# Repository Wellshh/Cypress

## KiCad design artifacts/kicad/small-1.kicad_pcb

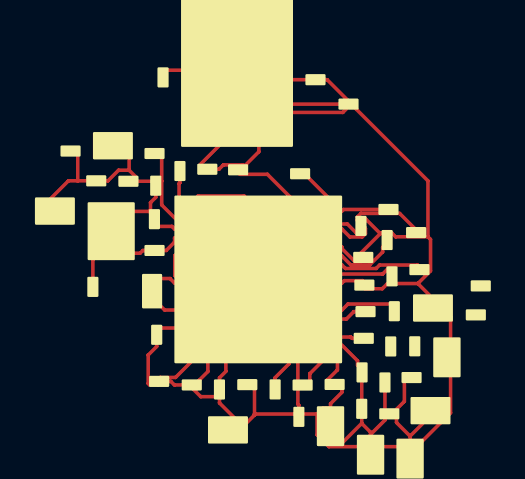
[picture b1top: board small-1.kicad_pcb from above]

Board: 2 copper layers, 57 parts (0 on the bottom side), 35 nets.

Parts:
C2779: C2779
C2781: C2781
C2782: C2782
C2783: C2783
C3780: C3780
C3782: C3782
C3783: C3783
C3784: C3784
C3785: C3785
C3786: C3786
C3787: C3787
C3788: C3788
C3789: C3789
C3790: C3790
C3791: C3791
C3792: C3792
C3795: C3795
C3796: C3796
C3797: C3797
C3798: C3798
C3799: C3799
C3800: C3800
C3801: C3801
C3802: C3802
C3803: C3803
C3804: C3804
C3824: C3824
LB55: LB55
R3729: R3729
R4389: R4389
R4390: R4390
R4392: R4392
R4553: R4553
R4556: R4556
R4557: R4557
R4566: R4566
R4568: R4568
R4570: R4570
R4571: R4571
R4573: R4573
R4574: R4574
R4575: R4575
R4576: R4576
R4577: R4577
R4578: R4578
R4579: R4579
R5027: R5027
R5029: R5029
R5677: R5677
R5820: R5820
R5821: R5821
R5823: R5823
R5908: R5908
R5909: R5909
U382: U382
U383: U383
Y7: Y7

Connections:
GP_I210_SPI_RST_L: R3729.1, U382.1
JTAG_I210_TDO: R5908.1, U383.25
L_I210_GBE0_LINK100_L: R5821.1, U383.28
L_I210_GBE0_LINK_ACT_L: R5823.1, U383.29
NET_1V5_I210: C3795.0, C3797.0, C3799.0, C3801.0, C3803.0, C3824.0, U383.5, U383.6, U383.7
NET_3V3_I210: C3782.0, C3785.0, C3786.0, C3787.0, C3788.0, C3789.0, C3790.0, C3791.0, LB55.0, U383.8, U383.9, U383.10, U383.11, U383.12
NET_3V3_I210_PMOS: C2782.0, C3780.0, LB55.1, R3729.0, R4566.0, R4568.0, R4571.0, R4573.0, R4575.0, R4577.0, R4579.0, R5027.0, R5029.0, R5821.0, R5823.0, R5908.0, R5909.0, U382.0
PCIE_I210_SOC_0AN_C: C3784.1, U383.32
PCIE_I210_SOC_0AP_C: C3783.1, U383.33
SE_I210_CBOT: C2783.0, U383.36
SE_I210_CTOP: C2783.1, U383.37
SE_I210_PCIE_DIS_L: R4566.1, U383.38
SE_I210_XTAL_IN: R5677.0, U383.39
SE_I210_XTAL_IN_R: C2779.0, R5677.1, Y7.0
SE_I210_XTAL_OUT: R4389.0, U383.40
SE_I210_XTAL_OUT_R: C2781.0, R4389.1, Y7.1
SE_NCSI_I210_CLK_IN: R4574.0, U383.41
SE_NCSI_I210_CRS_DV: R4576.0, U383.42
SE_NCSI_I210_RXD0: R4579.1, U383.43
SE_NCSI_I210_RXD1: R4577.1, U383.44
SE_NCSI_I210_TXD0: R4575.1, U383.45
SE_NCSI_I210_TXD1: R4573.1, U383.46
SE_NCSI_I210_TX_EN: R4578.0, U383.47
SE_SPI_I210_MISO_FLASH_R: R4553.1, U382.5
SE_SPI_I210_MUX_CLK_R: R4390.1, U383.48
SE_SPI_I210_MUX_CS_L_R: R4392.1, U383.49
SE_SPI_I210_MUX_MOSI_R: R4556.1, U383.51
SE_SPI_PROG_I210_HOLD_L_PU: R5029.1, U382.6
SE_SPI_PROG_I210_WP_L: R5027.1, U382.7
S_I210_CPLD_WAKE_L: R4568.1, U383.58
S_I210_DEV_OFF_L: R4571.1, U383.59
S_I210_PE_RST_L: R4570.0, U383.60
S_I210_RESET_L: R5820.0, U383.61
S_I210_RSET: R4557.0, U383.62
S_I210_SMB_ALERT_L: R5909.1, U383.63

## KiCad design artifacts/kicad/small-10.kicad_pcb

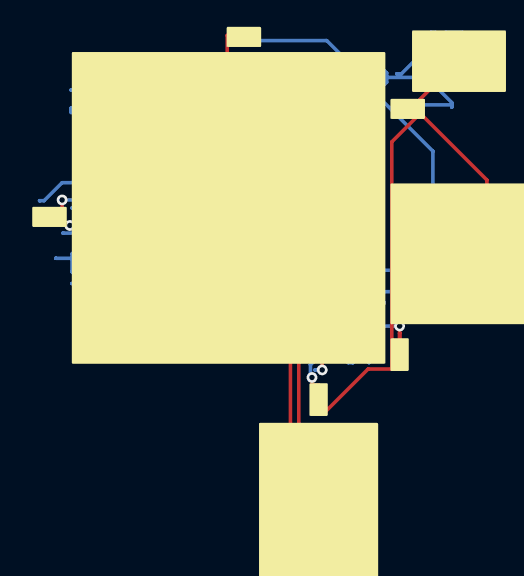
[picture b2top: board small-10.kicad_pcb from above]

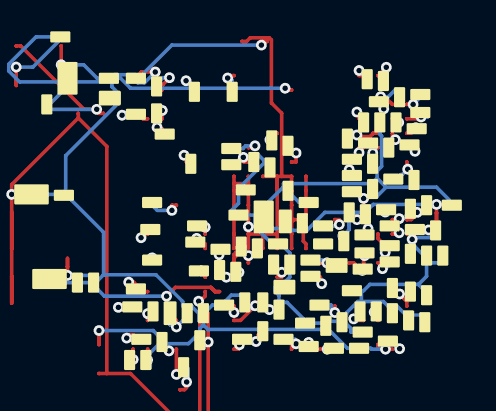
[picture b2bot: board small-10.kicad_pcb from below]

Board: 2 copper layers, 136 parts (127 on the bottom side), 93 nets.

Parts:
C226: C226
C232: C232
C233: C233
C234: C234
C235: C235
C236: C236
C237: C237
C238: C238
C239: C239
C240: C240
C241: C241
C242: C242
C243: C243
C244: C244
C245: C245
C246: C246
C247: C247
C248: C248
C249: C249
C250: C250
C251: C251
C252: C252
C253: C253
C254: C254
C255: C255
C3706: C3706
C3707: C3707
C3708: C3708
C4411: C4411
C4412: C4412
C4413: C4413
C4414: C4414
C4415: C4415
C4416: C4416
C4417: C4417
C4418: C4418
C4419: C4419
C4420: C4420
C4421: C4421
C4422: C4422
C4423: C4423
DS171: DS171
DS172: DS172
J10: J10
J169: J169
LB8: LB8
LB9: LB9
LB31: LB31
R1180: R1180
R1181: R1181
R1191: R1191
R1192: R1192
R1193: R1193
R1194: R1194
R1195: R1195
R1196: R1196
R1197: R1197
R1198: R1198
R1199: R1199
R1200: R1200
R1201: R1201
R1202: R1202
R1203: R1203
R1204: R1204
R1206: R1206
R1207: R1207
R1208: R1208
R1212: R1212
R1213: R1213
R1217: R1217
R1218: R1218
R1219: R1219
R1220: R1220
R1221: R1221
R1222: R1222
R1223: R1223
R1225: R1225
R1226: R1226
R1234: R1234
R1236: R1236
R1238: R1238
R1241: R1241
R1243: R1243
R1244: R1244
R1246: R1246
R1248: R1248
R1249: R1249
R1250: R1250
R1253: R1253
R1301: R1301
R1302: R1302
R2379: R2379
R2380: R2380
R2453: R2453
R2482: R2482
R2823: R2823
R2824: R2824
R2827: R2827
R3286: R3286
R3340: R3340
R3341: R3341
R3342: R3342
R3829: R3829
R3830: R3830
R4106: R4106
R4226: R4226
R4327: R4327
R4329: R4329
R4413: R4413
R4414: R4414
R4497: R4497
R4500: R4500
R4501: R4501
R4649: R4649
R4652: R4652
R4653: R4653
R4654: R4654
R4655: R4655
R4685: R4685
R4695: R4695
R4697: R4697
R4730: R4730
R4732: R4732
R4733: R4733
R4734: R4734
R4735: R4735
R4736: R4736
R4737: R4737
R4738: R4738
R4739: R4739
R4740: R4740
R4766: R4766
R4767: R4767
R4768: R4768
U55: U55
Y4: Y4

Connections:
AG_CPLD_FAN_PWM1_R: R1217.1, U55.31
AG_CPLD_FAN_PWM2_R: R1218.1, U55.32
AG_CPLD_FAN_PWM3_R: R1219.1, U55.33
AG_CPLD_FAN_PWM4_R: R1220.1, U55.34
GP_CEX_REFCLK1_EN: R3829.0, U55.50
GP_CLK_BRD1_RSRVD1_R: R2824.1, U55.55
GP_CLK_BRD1_RSRVD2_R: R4695.1, U55.56
GP_CLK_BRD2_RSRVD1_R: R4106.1, U55.60
GP_CLK_BRD2_RSRVD2_R: R4697.1, U55.61
GP_CPLD_CEX_GPI1_R: R1208.1, U55.66
GP_CPLD_CEX_GPI3_R: R1206.1, U55.68
GP_MAIN_CPLD_HW_REV1: R1234.0, U55.140
GP_MAIN_CPLD_HW_REV2: R1236.0, U55.141
GP_MAIN_CPLD_HW_REV3: R1238.0, U55.142
GP_MAIN_PORTS1_CPLD_FW_RST_L: R1212.0, U55.143
GP_MAIN_PORTS1_CPLD_RST_L: R2379.0, U55.144
GP_MAIN_PORTS2_CPLD_FW_RST_L: R1213.0, U55.145
GP_MAIN_PORTS2_CPLD_RST_L: R2380.0, U55.146
GP_MAIN_PORTS3_CPLD_FW_RST_L: R4652.0, U55.147
GP_MAIN_PORTS3_CPLD_RST_L: R4653.0, U55.148
GP_PPS_IN_LVL_EN_L_R: R4730.1, U55.150
GP_PPS_OUT_LVL_EN_L_R: R4732.1, U55.151
GP_SECURED_DIS_JUMPER: R4327.0, U55.160
GP_SECURED_DIS_JUMPER_IN: J169.2, R4327.1, R4329.0
GP_SPI_JUMPER1: J10.0, R1192.1, U55.163
GP_SPI_JUMPER2: J10.1, R1191.1, U55.164
GP_STRAP_FLASH_PRESENT_R: R1249.1, U55.165
I2C_ASIC_CPLD_M_MDC5_R: R1226.1, U55.176
I2C_ASIC_CPLD_M_MDIO5_R: R1225.1, U55.177
L_CPLD_JTAG_ENB: R1195.1, U55.192
L_CPLD_MAIN_SN_PU: R1253.1, U55.193
L_CPLD_M_DONE: R1194.1, U55.194
L_CPLD_M_INITN_L: C226.0, R1193.1, U55.195
L_CPLD_M_PROGRAMN_L: R1196.1, U55.196
L_MAIN_CPLD_LED0_L: R1180.0, U55.210
L_MAIN_CPLD_LED0_L_R: DS171.1, R1180.1
L_MAIN_CPLD_LIVE_LED_L: R1181.0, U55.211
L_MAIN_CPLD_LIVE_LED_L_R: DS172.1, R1181.1
NET_1V8_VDDIO: C244.0, C246.0, C248.0, LB9.1
NET_3.3V_CPLD_MAIN: C235.0, C236.0, C237.0, C238.0, C239.0, C240.0, C241.0, C242.0, C243.0, C245.0, C247.0, C249.0, C250.0, C252.0, C254.0, C4411.0, C4412.0, C4413.0, C4414.0, C4415.0, C4416.0, C4417.0, C4418.0, C4419.0, C4420.0, C4421.0, C4422.0, C4423.0, LB8.0, U55.2, U55.3, U55.4, U55.5, U55.6, U55.7, U55.8, U55.9, U55.10, U55.11, U55.12, U55.13, U55.14, U55.15, U55.16, U55.17, U55.18, U55.19, U55.20, U55.21, U55.22, U55.23, U55.24, U55.25, U55.26, U55.27, U55.28, U55.29, U55.30
NET_3V3_AUX: C232.0, C233.0, C234.0, C3706.0, DS171.0, DS172.0, J169.0, J169.1, LB8.1, LB31.0, R1191.0, R1192.0, R1193.0, R1194.0, R1195.0, R1196.0, R1253.0, R3340.0, R3830.0
SE_CLK_BRD1_OE_L_R: R4733.1, U55.221
SE_CLK_BRD1_PROGRAM_EN_L_R: R4740.1, U55.222
SE_CLK_BRD1_PWR_EN_R: R4736.1, U55.223
SE_CLK_BRD2_OE_L_R: R4734.1, U55.224
SE_CLK_BRD2_PROGRAM_EN_L_R: R4739.1, U55.225
SE_CLK_BRD2_PWR_EN_R: R4735.1, U55.226
SE_CPLD_LPC_AD0: R1199.0, U55.227
SE_CPLD_LPC_AD1: R1200.0, U55.228
SE_CPLD_LPC_AD2: R1201.0, U55.229
SE_CPLD_LPC_AD3: R1202.0, U55.230
SE_CPLD_LPC_CLK: R1203.0, U55.231
SE_CPLD_LPC_FRAME_L: R1198.0, U55.232
SE_CPLD_LPC_SERIRQ: R1197.0, U55.233
SE_CPLD_MAIN_OSC_OE: R3340.1, Y4.0
SE_OSC_CPLD_OUT: R3341.0, U55.235
SE_OSC_CPLD_OUT_R: R3341.1, Y4.1
SE_SR_CAPTURE_CPLD_MAIN_PORTS1_R: R4766.1, U55.237
SE_SR_CAPTURE_CPLD_MAIN_PORTS2_R: R4767.1, U55.238
SE_SR_CAPTURE_CPLD_MAIN_PORTS3_R: R4768.1, U55.239
SE_SR_CLK_CPLD_MAIN_PORTS1_R: R1243.1, U55.241
SE_SR_CLK_CPLD_MAIN_PORTS2_R: R3286.1, U55.242
SE_SR_CLK_CPLD_MAIN_PORTS3_R: R4649.1, U55.243
SE_SR_DATA_CPLD_MAIN_PORTS1_R: R1221.1, U55.245
SE_SR_OK_OUT_CPLD_MAIN_PORTS1: R1241.1, U55.246
SE_SYNCB_CPLD_M_CEX_DATA_R: R1204.1, U55.250
SE_SYNCB_CPLD_M_P1_CLK_R: R1244.1, U55.251
SE_SYNCB_CPLD_M_P1_DATA_R: R1223.1, U55.252
SE_SYNCB_CPLD_M_P2_CLK_R: R1302.1, U55.253
SE_SYNCB_CPLD_M_P2_DATA_R: R1301.1, U55.254
SE_SYNCB_CPLD_M_P3_CLK_R: R4655.1, U55.255
SE_SYNCB_CPLD_M_P3_DATA_R: R4654.1, U55.256
SE_UART0_CPLD_CEX_R: R1246.1, U55.261
SE_UART0_CPLD_RJ45_R: R3342.1, U55.262
S_ASIC_PERST_L_R: R1248.1, U55.304
S_ASIC_PRE_RST_L_R: R1250.1, U55.305
S_CEX_PWRBTN_L: R1207.0, U55.309
S_CLK_BRD1_BOOT_DONE_I2C_EN_L_R: R4737.1, U55.310
S_CLK_BRD1_CI_SEL_L_R: R4500.1, U55.311
S_CLK_BRD1_RST_L_R: R2823.1, U55.316
S_CLK_BRD2_BOOT_DONE_I2C_EN_L_R: R4738.1, U55.317
S_CLK_BRD2_CI_SEL_L_R: R4501.1, U55.318
S_CLK_BRD2_RST_L_R: R2827.1, U55.323
S_CPLD_ASIC_RST_L: R4226.1, U55.324
S_CPLD_CEX_SYS_RESET_L_R: R1222.1, U55.326
S_DVDD_T_EN: R2482.0, U55.329
S_EN_ALL_PPB_MAIN_PORTS1: R4414.0, U55.331
S_EN_ALL_PPB_MAIN_PORTS2: R4413.0, U55.332
S_EN_ALL_PPB_MAIN_PORTS3: R4685.0, U55.333
S_POWER_CTRL_VR_FAULT_L: R3830.1, U55.340
S_TILES_PRE_RST_L_R: R4497.1, U55.358
S_VDD_T_EN: R2453.0, U55.364
VIN_CPLD_EXT_OSC: C3707.0, C3708.0, LB31.1, Y4.2

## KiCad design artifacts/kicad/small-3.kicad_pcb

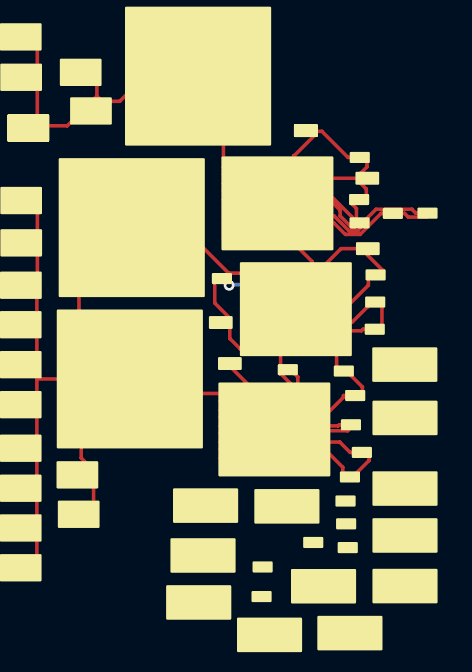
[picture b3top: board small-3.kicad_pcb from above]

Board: 2 copper layers, 63 parts (0 on the bottom side), 25 nets.

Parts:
C1_21_4: C1_21_4
C1_22_4: C1_22_4
C1_23_4: C1_23_4
C2_21_4: C2_21_4
C2_22_4: C2_22_4
C2_23_4: C2_23_4
C3_21_4: C3_21_4
C3_22_4: C3_22_4
C3_23_4: C3_23_4
C4_21_4: C4_21_4
C4_22_4: C4_22_4
C4_23_4: C4_23_4
C5_21_4: C5_21_4
C5_22_4: C5_22_4
C5_23_4: C5_23_4
C6_21_4: C6_21_4
C6_22_4: C6_22_4
C6_23_4: C6_23_4
C7_21_4: C7_21_4
C7_22_4: C7_22_4
C7_23_4: C7_23_4
C8_21_4: C8_21_4
C8_22_4: C8_22_4
C8_23_4: C8_23_4
C9_21_4: C9_21_4
C9_22_4: C9_22_4
C9_23_4: C9_23_4
C10_21_4: C10_21_4
C10_22_4: C10_22_4
C10_23_4: C10_23_4
C11_21_4: C11_21_4
C11_22_4: C11_22_4
C11_23_4: C11_23_4
C12_21_4: C12_21_4
C12_22_4: C12_22_4
C12_23_4: C12_23_4
C13_21_4: C13_21_4
C13_22_4: C13_22_4
C13_23_4: C13_23_4
C14_21_4: C14_21_4
C14_22_4: C14_22_4
C14_23_4: C14_23_4
C15_21_4: C15_21_4
C15_22_4: C15_22_4
C15_23_4: C15_23_4
L1_21_4: L1_21_4
L1_22_4: L1_22_4
L1_23_4: L1_23_4
R1_21_4: R1_21_4
R1_22_4: R1_22_4
R1_23_4: R1_23_4
R2_21_4: R2_21_4
R2_22_4: R2_22_4
R2_23_4: R2_23_4
R3_21_4: R3_21_4
R3_22_4: R3_22_4
R3_23_4: R3_23_4
R4_21_4: R4_21_4
R4_22_4: R4_22_4
R4_23_4: R4_23_4
U1_21_4: U1_21_4
U1_22_4: U1_22_4
U1_23_4: U1_23_4

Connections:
AG_PH_BOOTRC_45: C11_23_4.0, R4_23_4.0
AG_PH_BOOTRC_46: C11_22_4.0, R4_22_4.0
AG_PH_BOOTRC_47: C11_21_4.0, R4_21_4.0
AG_PH_BOOT_45: R4_23_4.1, U1_23_4.3
AG_PH_BOOT_46: R4_22_4.1, U1_22_4.3
AG_PH_BOOT_47: R4_21_4.1, U1_21_4.3
AG_PH_PHASE_45: C11_23_4.1, U1_23_4.4
AG_PH_PHASE_46: C11_22_4.1, U1_22_4.4
AG_PH_PHASE_47: C11_21_4.1, U1_21_4.4
AG_PH_SW_45: L1_23_4.0, U1_23_4.5, U1_23_4.6, U1_23_4.7, U1_23_4.8, U1_23_4.9, U1_23_4.10, U1_23_4.11, U1_23_4.12, U1_23_4.13, U1_23_4.14
AG_PH_SW_46: L1_22_4.0, U1_22_4.5, U1_22_4.6, U1_22_4.7, U1_22_4.8, U1_22_4.9, U1_22_4.10, U1_22_4.11, U1_22_4.12, U1_22_4.13, U1_22_4.14
AG_PH_SW_47: L1_21_4.0, U1_21_4.5, U1_21_4.6, U1_21_4.7, U1_21_4.8, U1_21_4.9, U1_21_4.10, U1_21_4.11, U1_21_4.12, U1_21_4.13, U1_21_4.14
DVDD_PL0_2: C9_23_4.0, C10_23_4.0, C12_23_4.0, C13_23_4.0, C14_23_4.0, C15_23_4.0, L1_23_4.1
HVDD_PL0_2: C9_21_4.0, C9_22_4.0, C10_21_4.0, C10_22_4.0, C12_21_4.0, C12_22_4.0, C13_21_4.0, C13_22_4.0, C14_21_4.0, C14_22_4.0, C15_21_4.0, C15_22_4.0, L1_21_4.1, L1_22_4.1
S_HVDD_PL0_TAO_4: R2_21_4.0, R2_22_4.0
S_PH_EN_45: R3_23_4.0, U1_23_4.22
S_PH_EN_46: R3_22_4.0, U1_22_4.22
S_PH_EN_47: R3_21_4.0, U1_21_4.22
S_PH_TAO_45: R2_23_4.1, U1_23_4.23
S_PH_TAO_46: R2_22_4.1, U1_22_4.23
S_PH_TAO_47: R2_21_4.1, U1_21_4.23
S_PH_VCC_45: C7_23_4.0, R1_23_4.0, R3_23_4.1, U1_23_4.24
S_PH_VCC_46: C7_22_4.0, R1_22_4.0, R3_22_4.1, U1_22_4.24
S_PH_VCC_47: C7_21_4.0, R1_21_4.0, R3_21_4.1, U1_21_4.24
VDRV: C5_21_4.0, C5_22_4.0, C5_23_4.0, R1_21_4.1, R1_22_4.1, R1_23_4.1, U1_21_4.25, U1_22_4.25, U1_23_4.25

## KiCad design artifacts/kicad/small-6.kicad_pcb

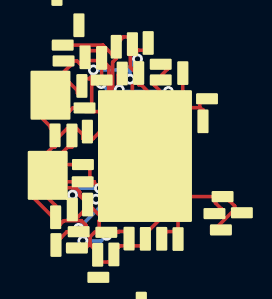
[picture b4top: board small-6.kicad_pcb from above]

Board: 2 copper layers, 46 parts (0 on the bottom side), 22 nets.

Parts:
C3501: C3501
C3502: C3502
C3503: C3503
C3504: C3504
C3505: C3505
C3520: C3520
C3521: C3521
C3522: C3522
C3523: C3523
Q18: Q18
Q19: Q19
R3913: R3913
R3914: R3914
R3915: R3915
R3917: R3917
R3918: R3918
R3919: R3919
R3920: R3920
R3921: R3921
R3922: R3922
R3923: R3923
R3924: R3924
R3927: R3927
R3928: R3928
R3929: R3929
R3930: R3930
R3931: R3931
R3932: R3932
R3933: R3933
R3934: R3934
R3935: R3935
R3937: R3937
R3938: R3938
R3939: R3939
R3958: R3958
R3959: R3959
R3960: R3960
R3961: R3961
R3962: R3962
R3963: R3963
R3964: R3964
R4004: R4004
R4006: R4006
R4007: R4007
R4008: R4008
U419: U419

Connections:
GP_1.8V_ASIC_QPS_FB: R3935.0, R3939.0
GP_1.8V_ASIC_QPS_REF: R3915.1, R3927.0, R3935.1, U419.4
GP_2.5V_OSC_EAST_FB: R3933.0, R3937.0
GP_2.5V_OSC_EAST_REF: R3913.1, R3931.0, R3933.1, U419.7
GP_2.5V_OSC_WEST_FB: R3934.0, R3938.0
GP_2.5V_OSC_WEST_REF: R3914.1, R3929.0, R3934.1, U419.8
GP_12VSB_COMP_REF: C3520.0, R4004.0, U419.5
GP_12VSB_COMP_REF_R: R3958.1, R3959.0, R4004.1
GP_12VSB_FB: R3963.0, R3964.0
GP_12VSB_REF: R3960.1, R3961.0, R3963.1, U419.6
NET_1.8V_ASIC_QPS_PG_SNS: C3521.0, R4006.1, U419.0
NET_2.5V_OSC_EAST_PG_SNS: C3523.0, R4008.1, U419.1
NET_2.5V_OSC_WEST_PG_SNS: C3522.0, R4007.1, U419.2
NET_3.3V_AUX: C3501.0, R3913.0, R3914.0, R3915.0, R3917.0, R3918.0, R3919.0, R3920.0, R3921.0, R3922.0, R3923.0, R3924.0, R3960.0, U419.3
S_1.8V_ASIC_QPS_PG: Q19.0, R3923.1
S_1.8V_ASIC_QPS_PG_L: C3504.0, Q19.1, R3919.1, R3939.1, U419.9
S_2.5V_OSC_ASIC_EAST_PG: Q18.0, R3921.1
S_2.5V_OSC_ASIC_EAST_PG_L: C3502.0, Q18.1, R3917.1, R3937.1, U419.11
S_2.5V_OSC_ASIC_WEST_PG: Q18.2, R3922.1
S_2.5V_OSC_ASIC_WEST_PG_L: C3503.0, Q18.3, R3918.1, R3938.1, U419.12
S_12VSB_PG: Q19.2, R3924.1
S_12VSB_PG_L: C3505.0, Q19.3, R3920.1, R3964.1, U419.10

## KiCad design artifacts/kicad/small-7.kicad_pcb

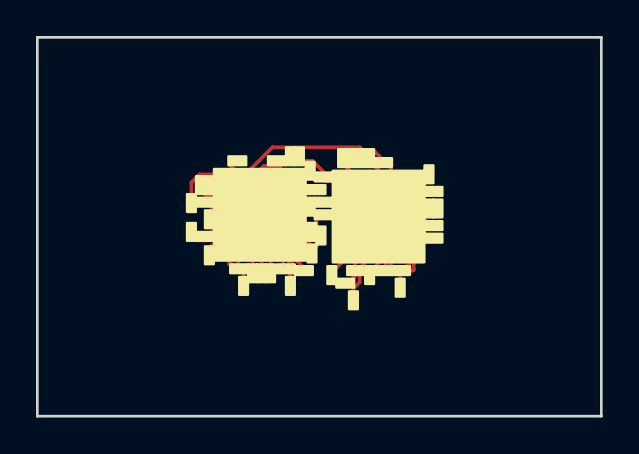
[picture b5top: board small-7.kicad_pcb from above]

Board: 2 copper layers, 31.3 x 21.0 mm, 50 parts (0 on the bottom side), 43 nets.

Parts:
C106: C106
C107: C107
C463: C463
C464: C464
R231: R231
R234: R234
R235: R235
R236: R236
R237: R237
R239: R239
R249: R249
R250: R250
R743: R743
R744: R744
R834: R834
R842: R842
R843: R843
R918: R918
R919: R919
R920: R920
R921: R921
R922: R922
R923: R923
R924: R924
R925: R925
R926: R926
R927: R927
R928: R928
R929: R929
R930: R930
R931: R931
R932: R932
R1017: R1017
R1018: R1018
R1060: R1060
R1061: R1061
R1062: R1062
R1063: R1063
R1064: R1064
R1065: R1065
R1066: R1066
R1067: R1067
R1238: R1238
R1239: R1239
R1240: R1240
R1241: R1241
R1242: R1242
R1365: R1365
U59: U59
U100: U100

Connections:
AD_GPIO_EXP_HALFA: R234.0, U59.2
AD_GPIO_EXP_HALFB: R231.1, U100.2
GP_ASIC1_STRAP_FLASH_PRSNT_GPIO_EXP: R1238.1, U59.3
GP_ASIC2_STRAP_FLASH_PRSNT_GPIO_EXP: R1239.1, U59.4
GP_ASIC_SOC_JTAG_BUF_EN_L_R: R1242.1, U100.3
GP_GPIO_EXP_RESET_L_R: R237.1, R239.1, U59.5, U100.4
GP_SPI_ASIC1_FW_BUF1_EN_L_R: R249.1, U100.5
GP_SPI_ASIC2_FW_BUF1_EN_L_R: R250.1, U100.6
GP_SW_I2C_MUXS_SEL_A_R: R743.1, U100.7
GP_SW_I2C_MUXS_SEL_B_R: R744.1, U100.8
I2C_TESTING_GPIO_SCL: R235.1, U59.6, U100.9
I2C_TESTING_GPIO_SDA: R236.1, U59.7, U100.10
S_1V8_CPLD_IO_EN_R: R1067.1, U59.9
S_1V8_QPS_EN_GPIO_EXP: R1365.1, U100.22
S_3V3_ASIC_EN_R: R1064.1, U59.10
S_3V3_CTRL_PWR_EN_R: R834.1, U59.11
S_3V3_OSC1_EN_R: R1062.1, U59.12
S_3V3_OSC2_EN_R: R1063.1, U59.13
S_5V_CLK1_EN_R: R1065.1, U59.14
S_5V_CLK2_EN_R: R1066.1, U59.15
S_ASIC1_RST_L_R: R1017.1, U59.16
S_ASIC1_TCXO_EN_R: R1241.1, U100.23
S_ASIC2_RST_L_R: R1018.1, U59.17
S_ASIC2_TCXO_EN_R: R1240.1, U100.24
S_CLK_BRD1_OE_L_R: R931.1, U100.25
S_CLK_BRD1_PROGRAM_EN_L_R: R928.1, U100.26
S_CLK_BRD1_PWR_EN_R: R842.1, U100.27
S_CLK_BRD2_OE_L_R: R932.1, U100.28
S_CLK_BRD2_PROGRAM_EN_L_R: R929.1, U100.29
S_CLK_BRD2_PWR_EN_R: R843.1, U100.30
S_DVDD_S0_ASIC1_EN_R: R921.1, U59.18
S_DVDD_S0_ASIC2_EN_R: R926.1, U59.19
S_DVDD_S1_ASIC1_EN_R: R922.1, U59.20
S_DVDD_S1_ASIC2_EN_R: R927.1, U59.21
S_HVDD_S0_ASIC1_EN_R: R919.1, U59.22
S_HVDD_S0_ASIC2_EN_R: R924.1, U59.23
S_HVDD_S1_ASIC1_EN_R: R920.1, U59.24
S_HVDD_S1_ASIC2_EN_R: R925.1, U59.25
S_MAIL_BOX_I2C_EN_GPIO_EXP_L: R930.0, U59.26
S_VDD_ASIC1_EN_R: R918.1, U59.27
S_VDD_ASIC2_EN_R: R923.1, U59.28
S_VDRV1_EN_R: R1060.1, U59.29
S_VDRV2_EN_R: R1061.1, U59.30

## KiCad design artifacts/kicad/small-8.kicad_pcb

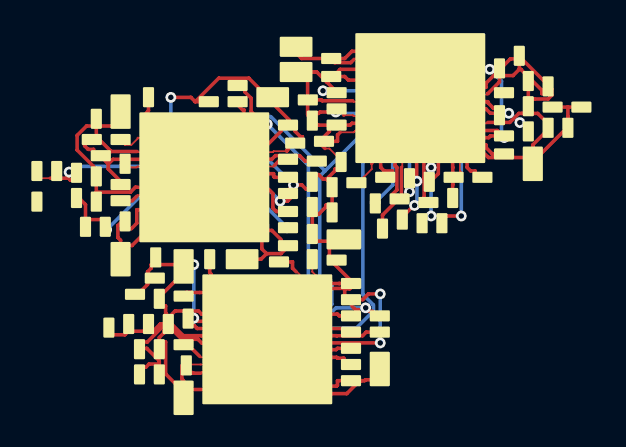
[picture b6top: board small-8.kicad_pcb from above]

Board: 2 copper layers, 115 parts (0 on the bottom side), 83 nets.

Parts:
C3_3: C3_3
C5_3: C5_3
C6_3: C6_3
C7_3: C7_3
C8_3: C8_3
C9_3: C9_3
C10_3: C10_3
C11_3: C11_3
C15_3: C15_3
C16_3: C16_3
C18_3: C18_3
C19_3: C19_3
C20_3: C20_3
C21_3: C21_3
C22_3: C22_3
C23_3: C23_3
C24_3: C24_3
C25_3: C25_3
C30_3: C30_3
C31_3: C31_3
C33_3: C33_3
C34_3: C34_3
C35_3: C35_3
C36_3: C36_3
C37_3: C37_3
C38_3: C38_3
C39_3: C39_3
C40_3: C40_3
R1_3: R1_3
R2_3: R2_3
R3_3: R3_3
R4_3: R4_3
R5_3: R5_3
R7_3: R7_3
R8_3: R8_3
R9_3: R9_3
R10_3: R10_3
R11_3: R11_3
R12_3: R12_3
R13_3: R13_3
R14_3: R14_3
R15_3: R15_3
R16_3: R16_3
R17_3: R17_3
R18_3: R18_3
R19_3: R19_3
R20_3: R20_3
R21_3: R21_3
R22_3: R22_3
R23_3: R23_3
R24_3: R24_3
R25_3: R25_3
R27_3: R27_3
R29_3: R29_3
R30_3: R30_3
R31_3: R31_3
R32_3: R32_3
R33_3: R33_3
R34_3: R34_3
R35_3: R35_3
R36_3: R36_3
R37_3: R37_3
R38_3: R38_3
R39_3: R39_3
R40_3: R40_3
R41_3: R41_3
R42_3: R42_3
R44_3: R44_3
R46_3: R46_3
R47_3: R47_3
R48_3: R48_3
R49_3: R49_3
R50_3: R50_3
R51_3: R51_3
R52_3: R52_3
R53_3: R53_3
R54_3: R54_3
R56_3: R56_3
R57_3: R57_3
R58_3: R58_3
R59_3: R59_3
R60_3: R60_3
R61_3: R61_3
R62_3: R62_3
R63_3: R63_3
R64_3: R64_3
R65_3: R65_3
R66_3: R66_3
R67_3: R67_3
R68_3: R68_3
R69_3: R69_3
R70_3: R70_3
R72_3: R72_3
R74_3: R74_3
R75_3: R75_3
R76_3: R76_3
R77_3: R77_3
R78_3: R78_3
R79_3: R79_3
R80_3: R80_3
R81_3: R81_3
R82_3: R82_3
R84_3: R84_3
R85_3: R85_3
R86_3: R86_3
R87_3: R87_3
R88_3: R88_3
R89_3: R89_3
R90_3: R90_3
R91_3: R91_3
R92_3: R92_3
R96_3: R96_3
U1_3: U1_3
U2_3: U2_3
U3_3: U3_3

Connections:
AG_DVDD_PL0_PWM_PH1_R_3: R49_3.1, U2_3.2
AG_DVDD_PL0_PWM_PH2_R_3: R50_3.1, U2_3.3
AG_DVDD_PL1_PWM_PH1_R_3: R77_3.1, U3_3.2
AG_DVDD_PL1_PWM_PH2_R_3: R78_3.1, U3_3.3
AG_HVDD_PL0_PWMVID_3: R48_3.0, U2_3.4
AG_HVDD_PL0_PWM_PH1_R_3: R52_3.1, U2_3.5
AG_HVDD_PL0_PWM_PH2_R_3: R51_3.1, U2_3.6
AG_HVDD_PL1_PWMVID_3: R76_3.0, U3_3.4
AG_HVDD_PL1_PWM_PH1_R_3: R80_3.1, U3_3.5
AG_HVDD_PL1_PWM_PH2_R_3: R79_3.1, U3_3.6
AG_VDD_PWM_PH1_R_3: R25_3.1, U1_3.10
AG_VDD_PWM_PH2_R_3: R24_3.1, U1_3.11
AG_VDD_PWM_PH3_R_3: R23_3.1, U1_3.12
AG_VDD_PWM_PH4_R_3: R22_3.1, U1_3.13
AG_VDD_PWM_PH5_R_3: R21_3.1, U1_3.14
AG_VDD_PWM_PH6_R_3: R20_3.1, U1_3.15
AG_VDD_PWM_PH7_R_3: R19_3.1, U1_3.16
AG_VDD_PWM_PH8_R_3: R18_3.1, U1_3.17
AG_VDD_PWM_PH9_R_3: R17_3.1, U1_3.18
AG_VDD_PWM_PH10_R_3: R16_3.1, U1_3.3
AG_VDD_PWM_PH11_R_3: R15_3.1, U1_3.4
AG_VDD_PWM_PH12_R_3: R14_3.1, U1_3.5
AG_VDD_PWM_PH13_R_3: R13_3.1, U1_3.6
AG_VDD_PWM_PH14_R_3: R12_3.1, U1_3.7
AG_VDD_PWM_PH15_R_3: R11_3.1, U1_3.8
AG_VDD_PWM_PH16_R_3: R10_3.1, U1_3.9
GP_HVDD_DVDD_S0_ASIC1_ALERT_L: R37_3.1, U2_3.7
GP_HVDD_DVDD_S1_ASIC1_ALERT_L: R65_3.1, U3_3.7
GP_VDD_ASIC1_ALERT_L: R1_3.1, U1_3.19
I2C_PMBUS_ASIC1_SCL: U1_3.20, U2_3.8, U3_3.8
I2C_PMBUS_ASIC1_SDA: U1_3.21, U2_3.9, U3_3.9
NET_3V3_CTRL: C5_3.0, C18_3.0, C33_3.0, R29_3.0, R56_3.0, R84_3.0
NET_3V3_CTRL_HVDD_DVDD_PL0_3: C19_3.0, C20_3.0, R37_3.0, R38_3.0, R40_3.0, R56_3.1, U2_3.0
NET_3V3_CTRL_HVDD_DVDD_PL1_3: C34_3.0, C35_3.0, R65_3.0, R66_3.0, R68_3.0, R84_3.1, U3_3.0
NET_3V3_CTRL_VDD_3: C6_3.0, C7_3.0, R1_3.0, R2_3.0, R4_3.0, R29_3.1, U1_3.0
S_DVDD_PL0_IMON_3: R42_3.0, U2_3.34
S_DVDD_PL0_SENSE_P_R_3: C16_3.0, R54_3.0, U2_3.37
S_DVDD_PL0_TAO_R_3: C25_3.0, R60_3.0, R62_3.1, U2_3.38
S_DVDD_PL0_VBOOT_3: R46_3.0, U2_3.39
S_DVDD_PL1_IMON_3: R70_3.0, U3_3.34
S_DVDD_PL1_SENSE_P_R_3: C31_3.0, R82_3.0, U3_3.37
S_DVDD_PL1_TAO_R_3: C40_3.0, R88_3.0, R90_3.1, U3_3.38
S_DVDD_PL1_VBOOT_3: R74_3.0, U3_3.39
S_DVDD_S0_ASIC1_EN: R41_3.0, U2_3.40
S_DVDD_S0_ASIC1_PG: R40_3.1, U2_3.41
S_DVDD_S0_ASIC1_SENSE_N: C16_3.1, U2_3.42
S_DVDD_S1_ASIC1_EN: R69_3.0, U3_3.40
S_DVDD_S1_ASIC1_PG: R68_3.1, U3_3.41
S_DVDD_S1_ASIC1_SENSE_N: C31_3.1, U3_3.42
S_HVDD_DVDD_PL0_ADDR_PMBUS_3: R63_3.0, R64_3.0, U2_3.43
S_HVDD_DVDD_PL0_VINSEN_3: C21_3.0, R58_3.0, R59_3.1, U2_3.45
S_HVDD_DVDD_PL1_ADDR_PMBUS_3: R91_3.0, R92_3.0, U3_3.43
S_HVDD_DVDD_PL1_VINSEN_3: C36_3.0, R86_3.0, R87_3.1, U3_3.45
S_HVDD_PL0_IMON_3: R47_3.0, U2_3.46
S_HVDD_PL0_SENSE_P_R_3: C15_3.0, R53_3.0, U2_3.49
S_HVDD_PL0_TAO_R_3: C23_3.0, R57_3.0, R61_3.1, U2_3.50
S_HVDD_PL0_VBOOT_3: R44_3.0, U2_3.51
S_HVDD_PL1_IMON_3: R75_3.0, U3_3.46
S_HVDD_PL1_SENSE_P_R_3: C30_3.0, R81_3.0, U3_3.49
S_HVDD_PL1_TAO_R_3: C38_3.0, R85_3.0, R89_3.1, U3_3.50
S_HVDD_PL1_VBOOT_3: R72_3.0, U3_3.51
S_HVDD_S0_ASIC1_EN: R39_3.0, U2_3.52
S_HVDD_S0_ASIC1_PG: R38_3.1, U2_3.53
S_HVDD_S0_ASIC1_SENSE_N: C15_3.1, U2_3.54
S_HVDD_S1_ASIC1_EN: R67_3.0, U3_3.52
S_HVDD_S1_ASIC1_PG: R66_3.1, U3_3.53
S_HVDD_S1_ASIC1_SENSE_N: C30_3.1, U3_3.54
S_VDD_ADDR_PMBUS_3: R35_3.0, R36_3.0, U1_3.22
S_VDD_ASIC1_EN: R3_3.0, U1_3.23
S_VDD_ASIC1_PG: R2_3.1, U1_3.24
S_VDD_ASIC1_SENSE_N: C3_3.0, U1_3.25
S_VDD_IMON_L1_3: R9_3.0, U1_3.26
S_VDD_IMON_L2_3: R5_3.0, U1_3.27
S_VDD_PG_L2_3: R4_3.1, U1_3.44
S_VDD_SENSE_P_R_3: C3_3.1, R27_3.1, U1_3.45
S_VDD_TAO_R_3: C11_3.0, R30_3.0, R34_3.1, U1_3.46
S_VDD_TSNS2_3: R33_3.0, U1_3.47
S_VDD_VBOOT2_3: R8_3.0, U1_3.48
S_VDD_VBOOT_3: R7_3.0, U1_3.49
S_VDD_VINSEN_3: C8_3.0, R31_3.0, R32_3.1, U1_3.51
S_VREF_HVDD_DVDD_PL0_3: C22_3.0, C24_3.0, R64_3.1, U2_3.55
S_VREF_HVDD_DVDD_PL1_3: C37_3.0, C39_3.0, R92_3.1, U3_3.55
S_VREF_VDD_3: C9_3.0, C10_3.0, R36_3.1, U1_3.52
